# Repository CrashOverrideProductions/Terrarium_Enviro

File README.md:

# Terrarium_Enviro
Reptile Terrarium Environment Management System

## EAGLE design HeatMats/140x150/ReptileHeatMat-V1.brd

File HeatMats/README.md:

# PCB HeatMats 

### Project: Low Temperature PCB Based HeatMats 

<!-- Repo Cover Image -->

<!-- Repo Stats -->

### Details
Lower Power / Temperature PCB Heat Mats based from 3D Printer Heat Beds

---
<!-- To Do List -->
### To Do List
- [ ] Complete Readme.md
- [ ] Build & Test Prototype
- [X] Design Schematic
- [ ] Finalise Software
- [X] Design Board
- [ ] Order Prototype PCBs

---
### Prototype Details
##### Hardware

##### Software

##### Hardware Configuration

<!-- Licencing Always at the Bottom -->

---

### Licencing 

**Creative Commons: Attribution - NonCommercial - ShareAlike 4.0 International (CC BY-NC-SA 4.0)**

**You are free to:**

**Share** — copy and redistribute the material in any medium or format

**Adapt** — remix, transform, and build upon the material

**Under the following terms:**

**Attribution** — You must give appropriate credit, provide a link to the license, and indicate if changes were made. You may do so in any reasonable manner, but not in any way that suggests the licensor endorses you or your use.

**NonCommercial** — You may not use the material for commercial purposes.

**ShareAlike** — If you remix, transform, or build upon the material, you must distribute your contributions under the same license as the original.

No additional restrictions — You may not apply legal terms or technological measures that legally restrict others from doing anything the license permits.

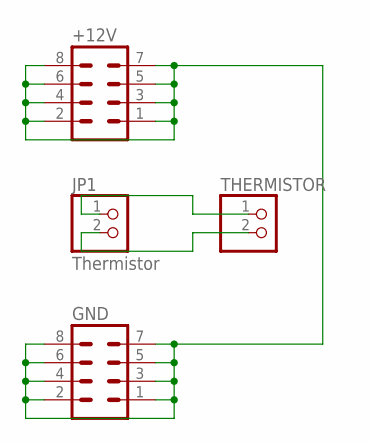
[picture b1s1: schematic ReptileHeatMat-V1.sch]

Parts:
+12V: MA04-2
GND: MA04-2
JP1: Thermistor; 1X02
THERMISTOR: PINHD-1X2; 1X02

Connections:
+12V: +12V.1, +12V.2, +12V.3, +12V.4, +12V.5, +12V.6, +12V.7, +12V.8, GND.1, GND.2, GND.3, GND.4, GND.5, GND.6, GND.7, GND.8
unnamed: JP1.2, THERMISTOR.2
unnamed: JP1.1, THERMISTOR.1

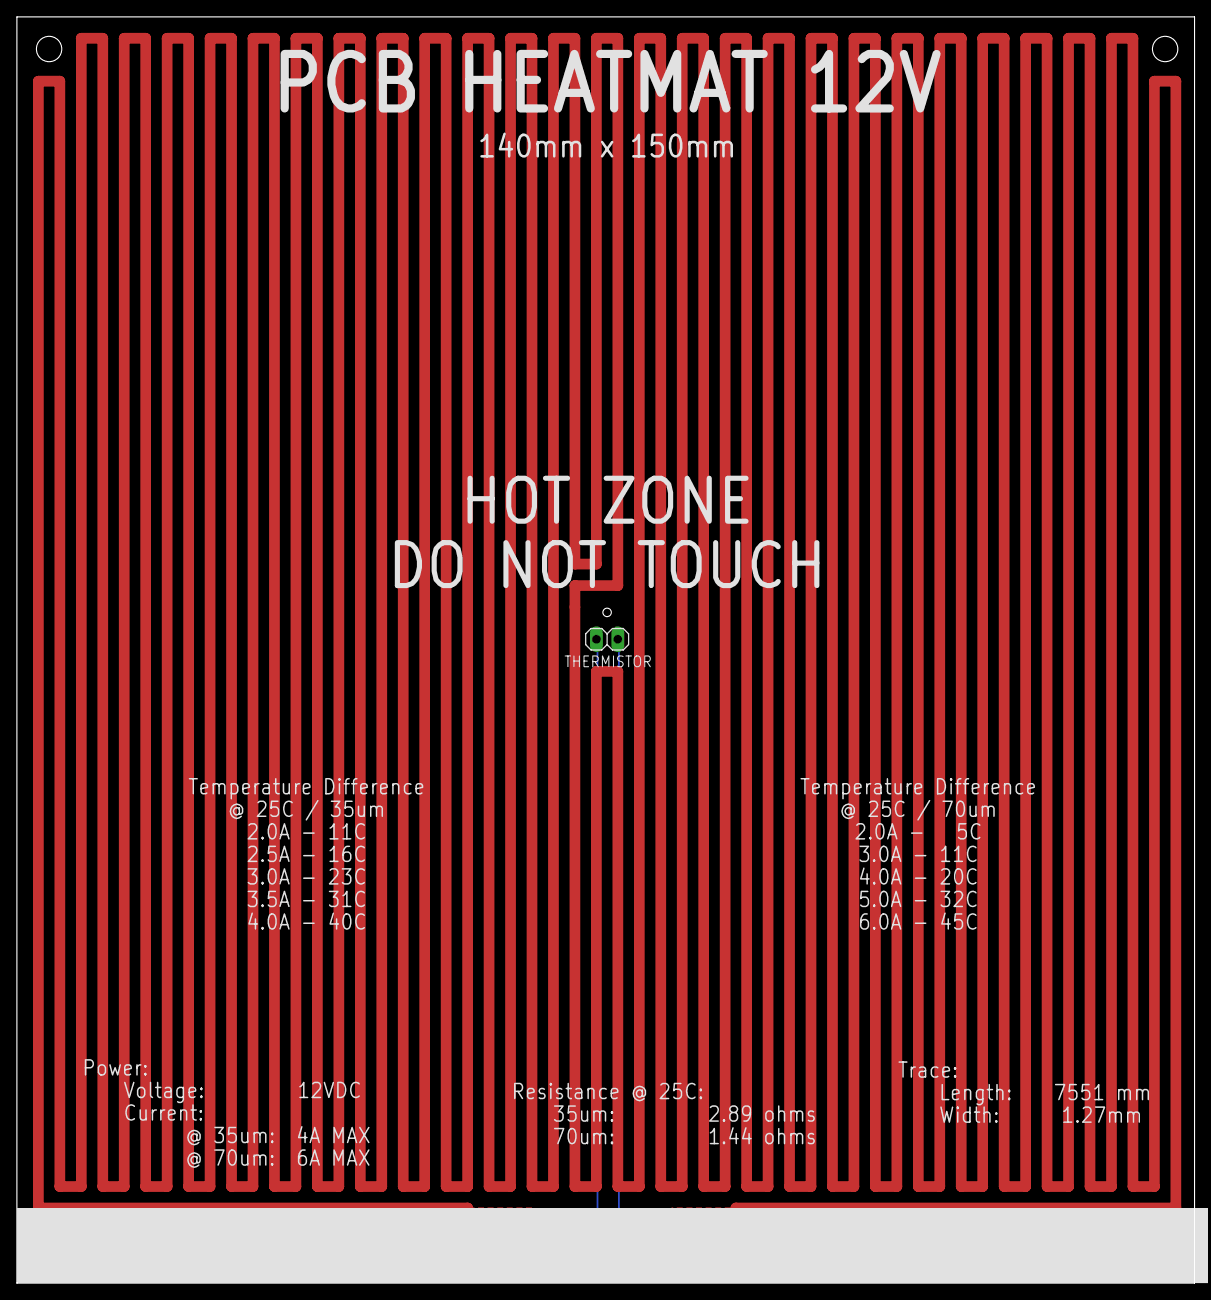
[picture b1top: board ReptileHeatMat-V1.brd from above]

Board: 2 copper layers, 139.4 x 149.8 mm, 4 parts (0 on the bottom side), 3 nets.

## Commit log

2021-06-22 inital

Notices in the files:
HeatMats/README.md:
License: CC-BY-NC-SA-4.0
